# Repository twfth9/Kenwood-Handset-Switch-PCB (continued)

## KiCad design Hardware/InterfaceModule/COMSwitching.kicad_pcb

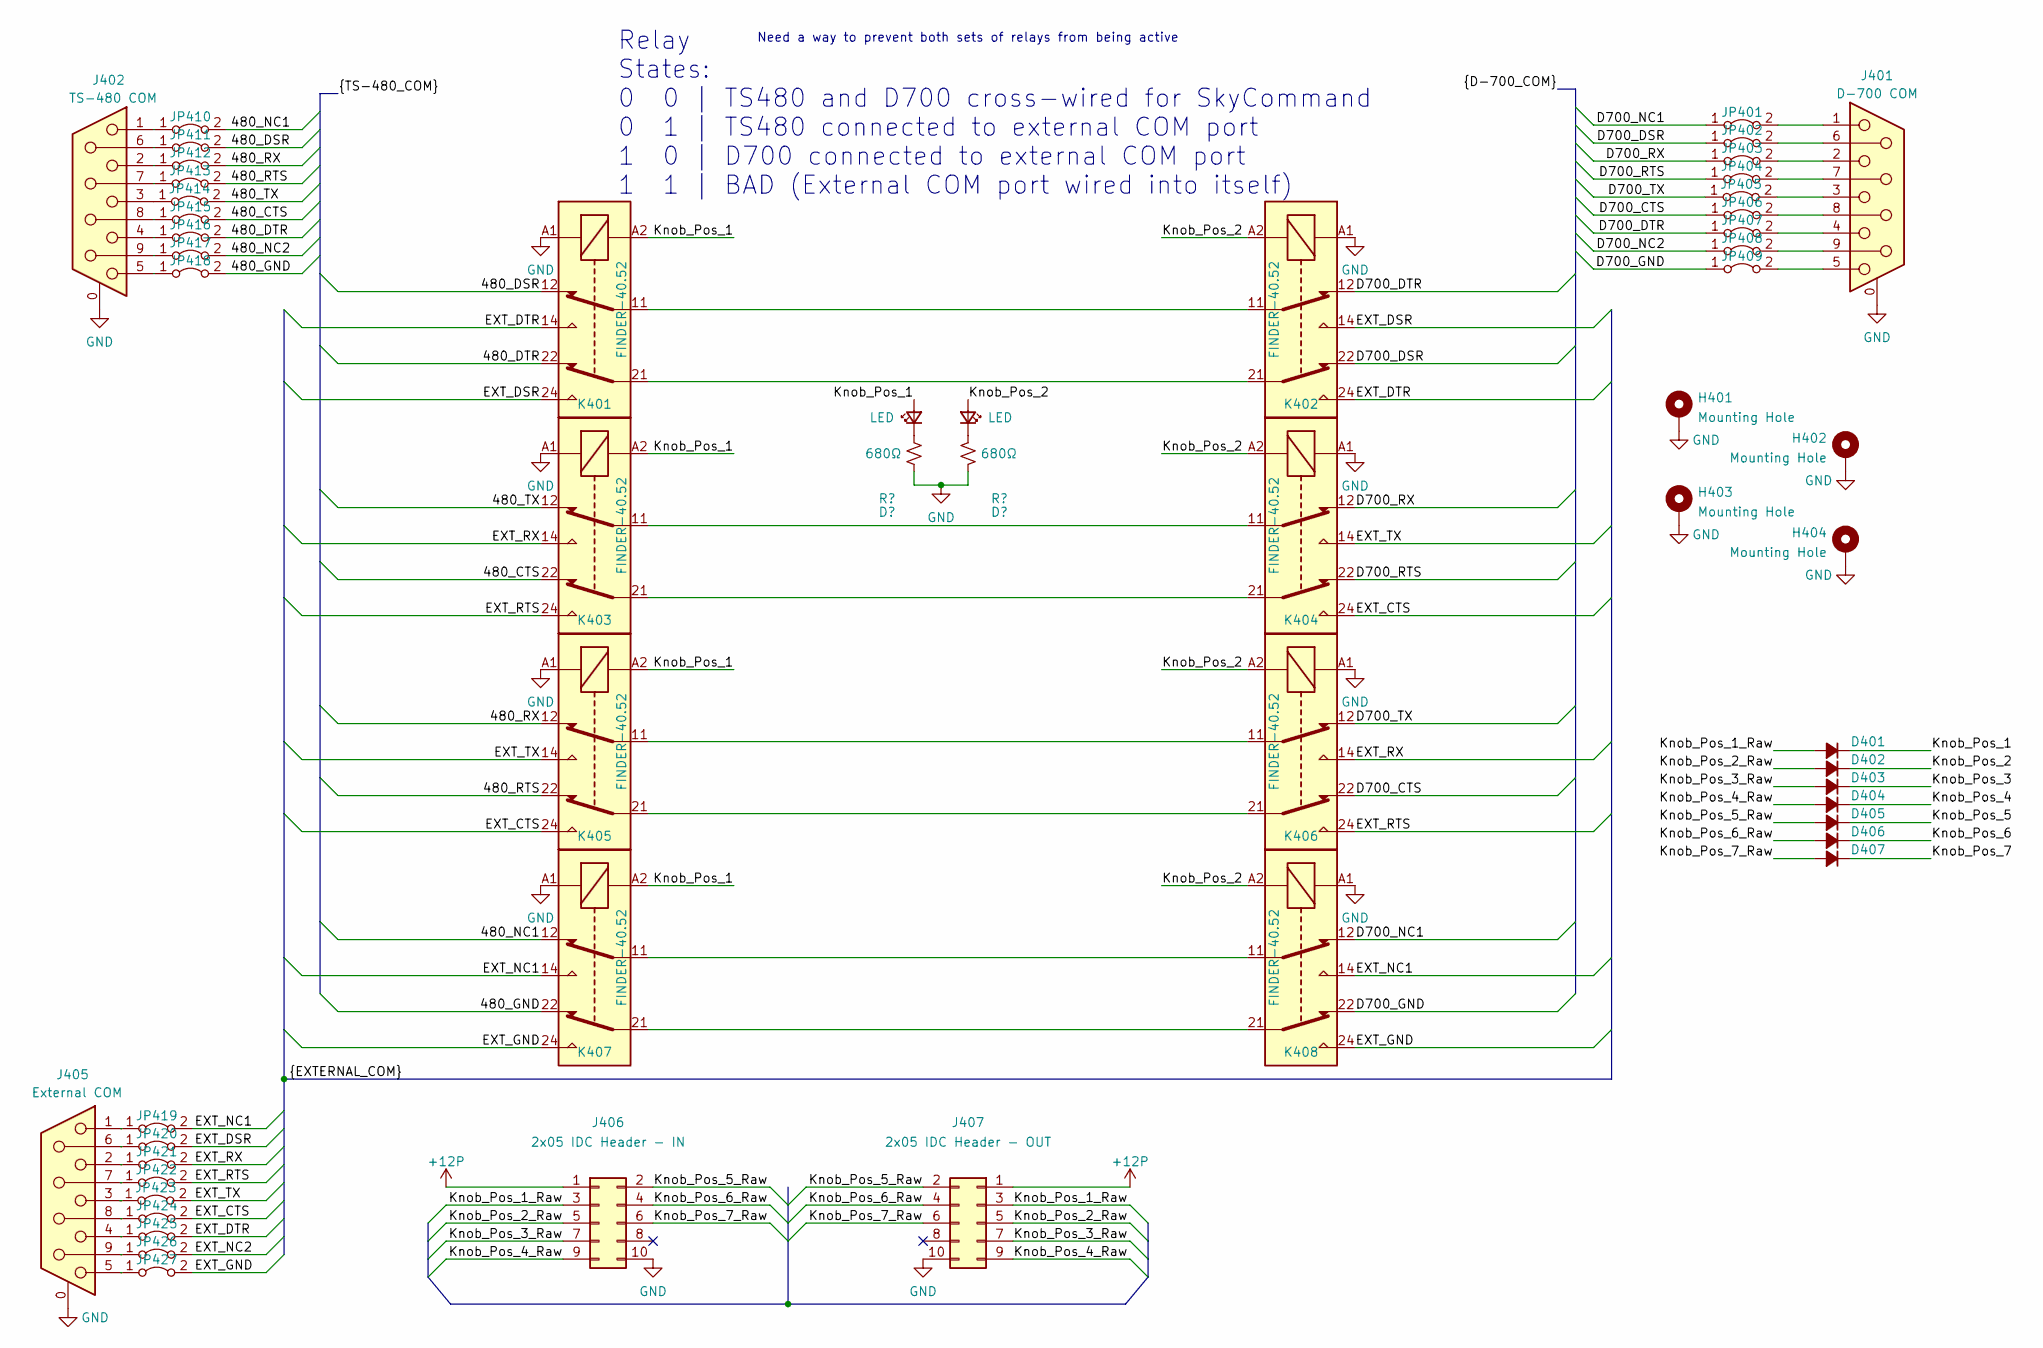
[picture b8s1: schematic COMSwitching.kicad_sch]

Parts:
D401, D402, D403, D404, D405, D406, D407: D_Small_Filled; D_A-405_P2.54mm_Vertical_AnodeUp
H401, H402, H403, H404: Mounting Hole; M3_Mounting
J401: D-700 COM; DSUB-9_Male_Horizontal_P2.77x2.84mm_EdgePinOffset7.70mm_Hou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
J402: TS-480 COM; DSUB-9_Male_Horizontal_P2.77x2.84mm_EdgePinOffset7.70mm_Hou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
J405: External COM; DSUB-9_Male_Horizontal_P2.77x2.84mm_EdgePinOffset7.70mm_Hou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
J406: 2x05 IDC Header - IN; IDC-Header_2x05_P2.54mm_Vertical
J407: 2x05 IDC Header - OUT; IDC-Header_2x05_P2.54mm_Vertical
JP401, JP402, JP403, JP404, JP405, JP406, JP407, JP408, JP409, JP410, JP411, JP412, JP413, JP414, JP415, JP416, JP417, JP418, JP419, JP420, JP421, JP422, JP423, JP424, JP425, JP426, JP427: Jumper_2_Bridged; 1.0mm_Bridge
K401, K402, K403, K404, K405, K406, K407, K408: FINDER-40.52; Relay_DPDT_Finder_30.22

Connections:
+12P: J406.1, J407.1
/COM Port Switching/480_CTS: JP415.2 (B), K403.22
/COM Port Switching/480_DSR: JP411.2 (B), K401.12
/COM Port Switching/480_DTR: JP416.2 (B), K401.22
/COM Port Switching/480_GND: JP418.2 (B), K407.22
/COM Port Switching/480_NC1: JP410.2 (B), K407.12
/COM Port Switching/480_NC2: JP417.2 (B)
/COM Port Switching/480_RTS: JP413.2 (B), K405.22
/COM Port Switching/480_RX: JP412.2 (B), K405.12
/COM Port Switching/480_TX: JP414.2 (B), K403.12
/COM Port Switching/D700_CTS: JP406.1 (A), K406.22
/COM Port Switching/D700_DSR: JP402.1 (A), K402.22
/COM Port Switching/D700_DTR: JP407.1 (A), K402.12
/COM Port Switching/D700_GND: JP409.1 (A), K408.22
/COM Port Switching/D700_NC1: JP401.1 (A), K408.12
/COM Port Switching/D700_NC2: JP408.1 (A)
/COM Port Switching/D700_RTS: JP404.1 (A), K404.22
/COM Port Switching/D700_RX: JP403.1 (A), K404.12
/COM Port Switching/D700_TX: JP405.1 (A), K406.12
/COM Port Switching/EXT_CTS: JP424.2 (B), K404.24, K405.24
/COM Port Switching/EXT_DSR: JP420.2 (B), K401.24, K402.14
/COM Port Switching/EXT_DTR: JP425.2 (B), K401.14, K402.24
/COM Port Switching/EXT_GND: JP427.2 (B), K407.24, K408.24
/COM Port Switching/EXT_NC1: JP419.2 (B), K407.14, K408.14
/COM Port Switching/EXT_NC2: JP426.2 (B)
/COM Port Switching/EXT_RTS: JP422.2 (B), K403.24, K406.24
/COM Port Switching/EXT_RX: JP421.2 (B), K403.14, K406.14
/COM Port Switching/EXT_TX: JP423.2 (B), K404.14, K405.14
/COM Port Switching/Knob_Pos_1: D401.1 (K), K401.A2, K403.A2, K405.A2, K407.A2; also elsewhere on the board
/COM Port Switching/Knob_Pos_1_Raw: D401.2 (A), J406.3, J407.3
/COM Port Switching/Knob_Pos_2: D402.1 (K), K402.A2, K404.A2, K406.A2, K408.A2; also elsewhere on the board
/COM Port Switching/Knob_Pos_2_Raw: D402.2 (A), J406.5, J407.5
/COM Port Switching/Knob_Pos_3: D403.1 (K)
/COM Port Switching/Knob_Pos_3_Raw: D403.2 (A), J406.7, J407.7
/COM Port Switching/Knob_Pos_4: D404.1 (K)
/COM Port Switching/Knob_Pos_4_Raw: D404.2 (A), J406.9, J407.9
/COM Port Switching/Knob_Pos_5: D405.1 (K)
/COM Port Switching/Knob_Pos_5_Raw: D405.2 (A), J406.2, J407.2
/COM Port Switching/Knob_Pos_6: D406.1 (K)
/COM Port Switching/Knob_Pos_6_Raw: D406.2 (A), J406.4, J407.4
/COM Port Switching/Knob_Pos_7: D407.1 (K)
/COM Port Switching/Knob_Pos_7_Raw: D407.2 (A), J406.6, J407.6
GND: H401.1, H402.1, H403.1, H404.1, J401.0 (PAD), J402.0 (PAD), J405.0 (PAD), J406.10, J407.10, K401.A1, K402.A1, K403.A1, K404.A1, K405.A1, K406.A1, K407.A1, K408.A1; also elsewhere on the board
unnamed: J401.1, JP401.2 (B)
unnamed: J401.2, JP403.2 (B)
unnamed: J401.3, JP405.2 (B)
unnamed: J401.4, JP407.2 (B)
unnamed: J401.5, JP409.2 (B)
unnamed: J401.6, JP402.2 (B)
unnamed: J401.7, JP404.2 (B)
unnamed: J401.8, JP406.2 (B)
unnamed: J401.9, JP408.2 (B)
unnamed: J402.1, JP410.1 (A)
unnamed: J402.2, JP412.1 (A)
unnamed: J402.3, JP414.1 (A)
unnamed: J402.4, JP416.1 (A)
unnamed: J402.5, JP418.1 (A)
unnamed: J402.6, JP411.1 (A)
unnamed: J402.7, JP413.1 (A)
unnamed: J402.8, JP415.1 (A)
unnamed: J402.9, JP417.1 (A)
unnamed: J405.1, JP419.1 (A)
unnamed: J405.2, JP421.1 (A)
unnamed: J405.3, JP423.1 (A)
unnamed: J405.4, JP425.1 (A)
unnamed: J405.5, JP427.1 (A)
unnamed: J405.6, JP420.1 (A)
unnamed: J405.7, JP422.1 (A)
unnamed: J405.8, JP424.1 (A)
unnamed: J405.9, JP426.1 (A)
unnamed: K401.11, K402.11
unnamed: K401.21, K402.21
unnamed: K403.11, K404.11
unnamed: K403.21, K404.21
unnamed: K405.11, K406.11
unnamed: K405.21, K406.21
unnamed: K407.11, K408.11
unnamed: K407.21, K408.21

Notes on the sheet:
Need a way to prevent both sets of relays from being active
Relay States: 0 0 | TS480 and D700 cross-wired for SkyCommand 0 1 | TS480 connected to external COM port 1 0 | D700 connected to external COM port 1 1 | BAD (External COM port wired into itself)

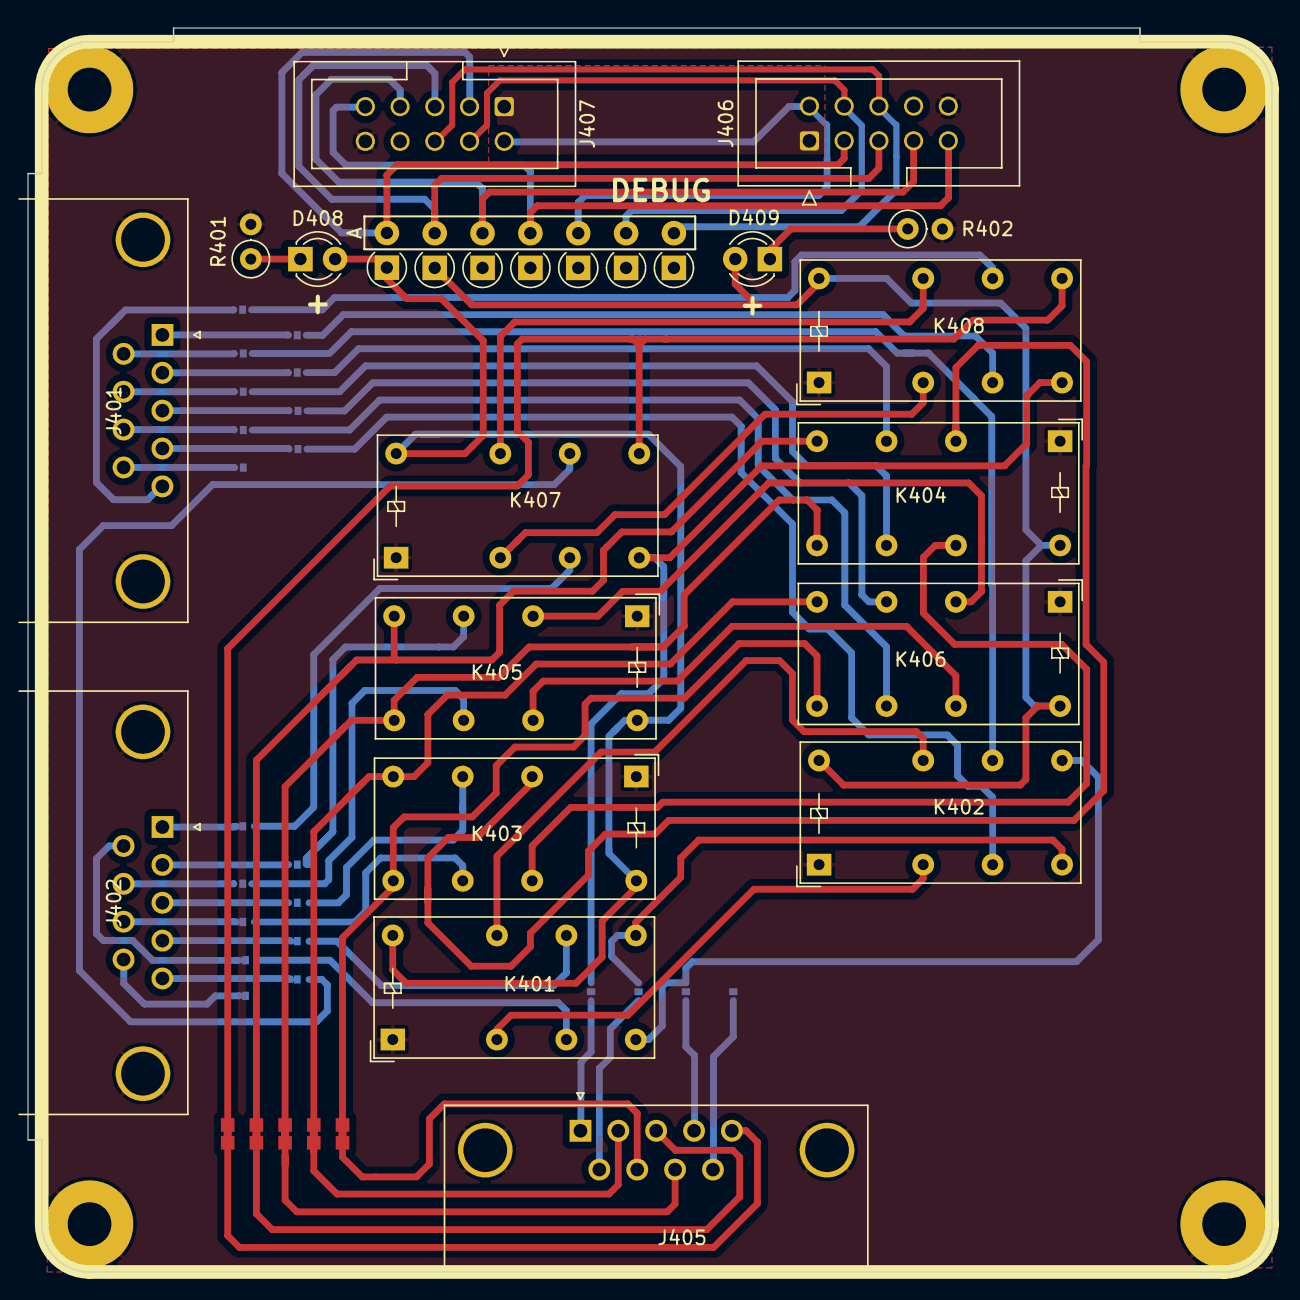
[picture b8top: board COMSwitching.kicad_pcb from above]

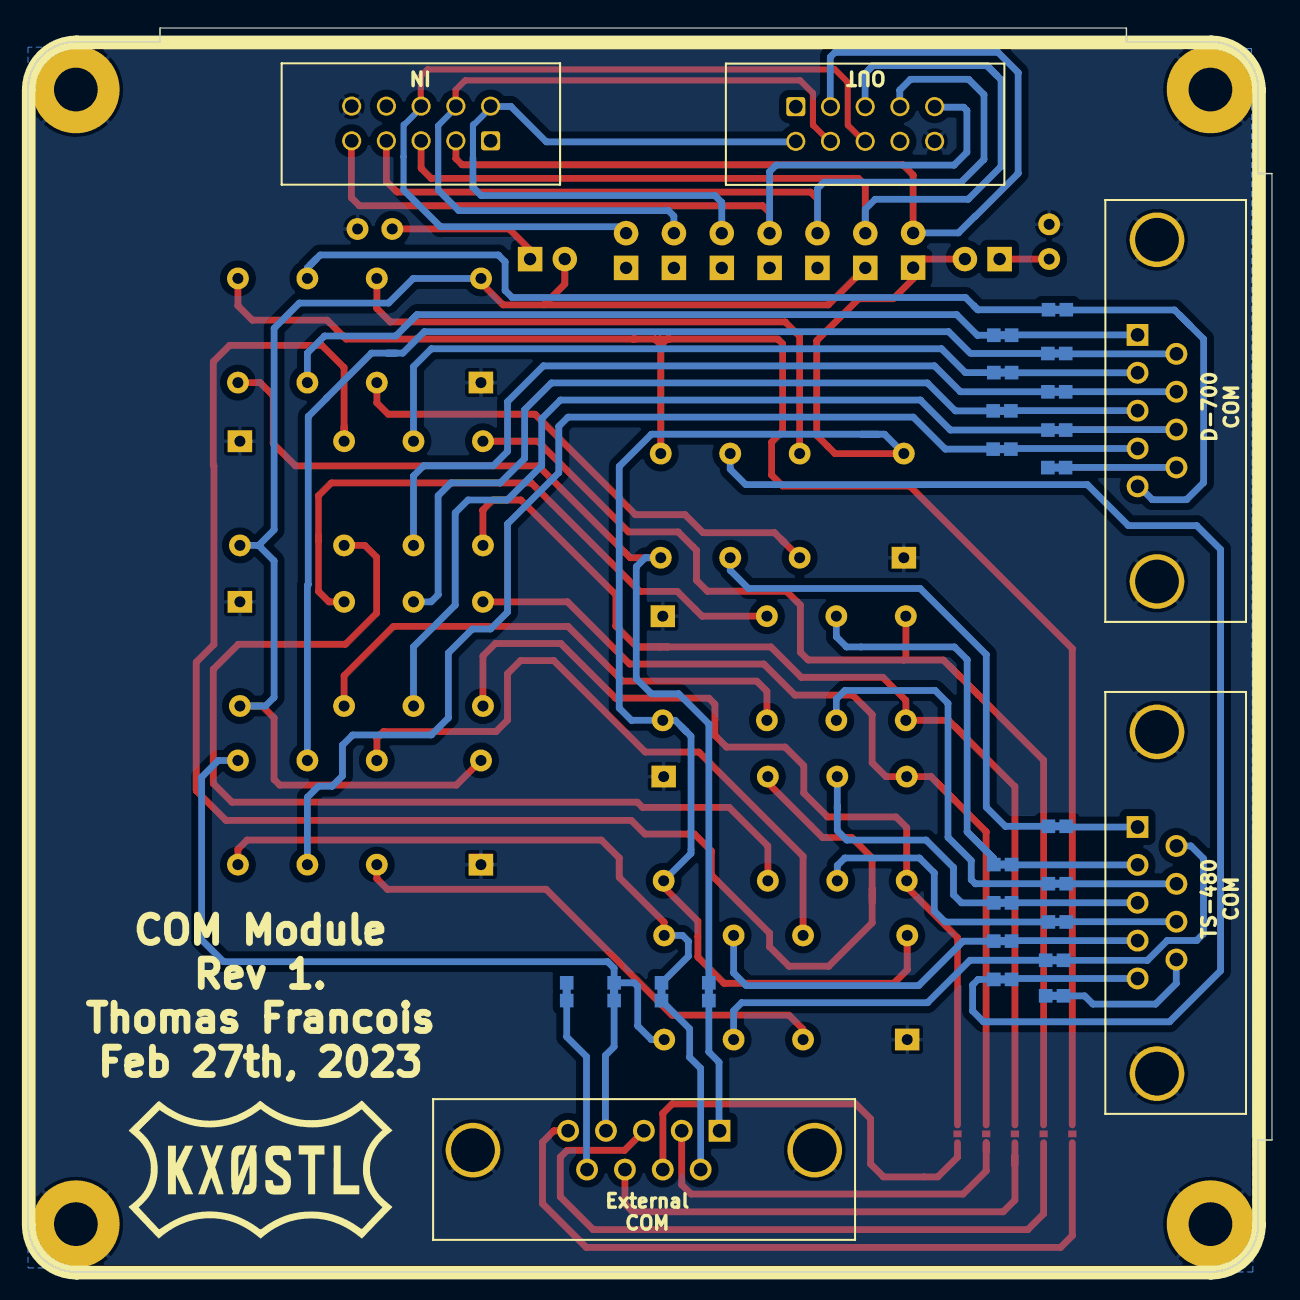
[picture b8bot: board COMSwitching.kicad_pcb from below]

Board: 2 copper layers, 91.0 x 91.0 mm, 55 parts (22 on the bottom side), 72 nets.

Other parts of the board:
D408, D409: LED; LED_D3.0mm
R401, R402: 680Ω; R_Axial_DIN0207_L6.3mm_D2.5mm_P2.54mm_Vertical

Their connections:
/COM Port Switching/Knob_Pos_1: D408.2 (A); also elsewhere on the board
/COM Port Switching/Knob_Pos_2: D409.2 (A); also elsewhere on the board
GND: R401.2, R402.2; also elsewhere on the board
unnamed: D408.1 (K), R401.1
unnamed: D409.1 (K), R402.1

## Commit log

2023-01-16 Created rough PCB
    GND on one relay needs to be fixed
2023-01-16 Updated layout, fixed ground islands
2023-01-29 Adjusted trace spacings
2023-01-30 Created PCB for KrakenSDR disconnect relay board, rearranged file structure
2023-01-30 New design as passthrough Kraken hat
2023-01-30 Created slim THRU and daughterboard cover
2023-01-30 Created ThinThru version of the board
2023-01-31 Created master switching pcb, com and mic relay circuits
2023-02-01 Connections for data ports, gps, improved mic connections
2023-02-01 Picked some footprints for most connectors
2023-02-02 Redesigned layout and labels
2023-02-02 More cleaning
2023-02-04 Fixed labels
    I don't know how to do busses properly, oh well
2023-02-04 Added selector input
2023-02-04 Replaced all relays with DPDT
2023-02-12 Broke out switching to individual boards
2023-02-20 Added backplane between boards, redesigned selector
2023-02-20 Initial routings of data and main boards
2023-02-20 Routed mic board
2023-02-21 Rerouted main and mic boards
    Might redo main board, it works but looks gross
2023-02-22 Routed data board
2023-02-26 Finished routing all 4 boards
2023-02-26 Complete routing, added debug pads/bridges
2023-02-26 Panelized boards
2023-02-26 Tweaked some things
2023-02-26 Tweaked more things
2023-02-26 Tweaks
2023-02-26 Even more tweaks
2023-02-26 cleaned some traces, changed tolerances, and copper pours
2023-02-27 Added LEDs
2023-03-04 Added silkscreen logos
2023-03-04 Generated gerber files
2023-03-05 Updated silkscreen dates, corrected gerber files
2023-12-29 Panel Dimensions to PCB
2023-12-29 Initial Schematic Work
2023-12-29 Schematic progress
2024-01-01 Added Instrumentation Amplifier To Schematic
2024-01-01 Assigned footprints, expanded schematic
2024-01-02 Changed to 14-segement Characters
2024-01-03 Added to schematic
2024-01-03 Added footprints and sectioned the schematic
    Still need to make sub pages and make a footprint for the MAX chips
2024-01-03 Scooted some stuffs
2024-01-03 Adjusted mode LEDs
2024-01-03 Added footprints to pcb file
    Need a proper footprint for the 14-seg LEDs, MAX driver chips...and something else that I can't remember right now
2024-01-08 Organized schematic into two pages, begun PCB routing
2024-01-08 Finished routing of rear board
2024-01-09 Routed most of the front panel
2024-01-10 Most of top board is routed
2024-01-10 beep
2024-01-14 Finished routing front panel
    Realized that I don't know how optocouplers work, so I need to replace them with transistors or something now
2024-01-14 Beginning to transition to BJTs
2024-01-15 Fixed BJT math
2024-01-15 Almost done with routing
2024-01-15 Finished routing
    Now just need to combine the boards with mousebites
2024-01-15 Modified front board to include cutout for rotate pot
2024-01-18 Rearranged pcb into production form, moved connector on top board
2024-04-05 Small tweaks to PCB
2024-04-07 More tweaks and silkscreen labels
2025-06-02 Audio Panel Progress
2025-06-03 Fixed undefined LED_IN net
2025-06-04 Added subsheets for audio panel
2025-06-04 Added symbols for crosspoint switches
2025-06-05 Added MT8816 crosspoint switch subsheet
2025-06-07 Added headphone and speaker jack interfaces
2025-06-09 Added crosspoints for each connector
2025-06-11 Added stupid Up,Down,PTT switching circuits
    I realize now this is very stupid, and I should just do this with a single GPIO expander IC
2025-06-11 Added MIC port protection
2025-06-12 Added MIC port protections
2025-06-12 Added 232 protections
2025-06-13 Early attempt at COM switching ideas
2025-06-13 Created COM switching using bilateral switches
    This feels stupid...but these chips are really cheap and actually pretty small. I know I say it now, but I'll pay for it when it comes time to do the routing :P
2025-06-13 Revisiting the audio input buffer circuit
2025-06-15 Added DSP chips, practicing with bus lines
2025-06-16 Added group labels
2025-06-16 Added MIC PTT UP DOWN sensing and buffering
2025-06-16 Replaced microphone page bs with an ADC and DAC
2025-06-17 Simplified COM switching, added USB-232
2025-06-17 small stuff
2025-06-17 Added main +5V supply with current sensing
2025-06-17 Added ideal diode controller to main power input
2025-06-18 Adding ADAV400 sheet
2025-06-18 Added USB hub, completed ADAV400 sheet, working on USBi programmer connections
2025-06-18 Added initial DB audio out connector
    Need to pick the best way to convert single-ended audio to differential
2025-06-18 Realized that I need to rethink how I'm going to mix the radio audio with the stereo audio
2025-06-19 Added MT8816 for audio switching
2025-06-19 Adjusted MIC input to crosspoint switch
2025-06-20 Added DATA switching to COM switching page
2025-06-20 Cleaned up stuff, defined more busses
2025-06-20 Removed extraneous pages
2025-06-20 Laid groundwork for stereo DSP routing
    I figured it out. I need to combine the left audio channels, combine the right audio channels, pass both to the DSP chips. Each audio zone will eventually have its own DSP to handle crossovers and ti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
    Use the Pioneer Network Mode for easier frequency separation.
    To do: add active summing amplifers to combine left and right sub-channels
2025-06-20 Added audio sum amplifiers
2025-06-21 Added speaker and headphone audio switching
2025-06-22 I forgot what I changed today, but it was some stuff
2025-06-23 Cleaned up sheet voltage inputs
2025-06-23 Considering replacing some of the MCP23017s with 74HC594 shift register
    Ken KC9UMR gave me this idea, would be cheaper option
2025-06-25 Added PCM2904 audio codec
2025-06-30 Moved files around, getting ready to design development modules
2025-06-30 Added microphone switcher initial schematic
2025-07-06 Finished most if not all of the microphone dev board
2025-07-07 Removed DAC and buffers for PTT, added PTT LEDs and inverters
2025-07-08 Assigned (most) footprints
2025-07-08 Changed LEDs to 0603 SMDs
2025-07-08 Rearranged LEDs, placed components onto PCB file
2025-07-08 Missed some LEDs, now SMD
2025-07-08 Changed WS2813Bs to WS2812B-2020s
    To reduce footprint size
2025-07-08 Changed resistor arrays to SMD
2025-07-09 Added stuff and things
2025-07-09 Finished assigning footprints
    No errors in PCB import, woo!
2025-07-09 Fixed 3bridge footprint
    Removed solder mask between pads
2025-07-09 Removed silkscreen component identifiers
2025-07-11 Started work on COM switching dev board
2025-07-11 Added power and USB serial
2025-07-12 Replaced MCPs with SAMD21G15
    The I2C bus was going to be too slow to handle the 232 timing required. I couldn't think of a cheaper way of doing it than just throwing a SAMD on there and calling it a day
2025-07-13 Added USB hub, new inverting LED indicator
2025-07-13 Added some stuff, don't remember what
2025-07-13 Fixed some more stuff
2025-07-13 Defined footprints for every component
2025-07-13 More things
2025-07-14 Assigned footprints
2025-07-14 Added test points for data ports, for real this time
2025-07-15 Adding shift registers to COM swicher
2025-07-16 Added shift registers to SPI
2025-07-16 Started replacing MCP23017 with shift registers
2025-07-16 Added stuff
    I just realized that the UP, DWN, PTT buttons should be powered by the radios.
    This means that I can get rid of the DAC, and just output to a voltage divider to generate the voltages.
    The radios have tons of 47k resistors on these lines so driving a lot of current isn't a requirement
2025-07-17 added stuff
2025-07-19 Changing mic switcher to use shift registers
2025-07-20 Finished most of microphone switcher circuit
    I'm very happy with where this is right now, I don't see anything immediately out of place and the schematic is now pretty well organized
2025-07-21 Isolated mic outputs to their respective radios
    Button presses are easy to isolate with optocouplers, I'm coupling in the mic signals using dc blocking capacitors and generating the bias voltages from the respective radios
2025-07-21 Added esd diodes to mic lines
    This shouldn't effect the audio signal because the voltage is +-5mV at this point, and the diode standoff voltages are at 5V
2025-07-22 Added labeling and organized pages
2025-07-22 COM Swicher changes and MIC Switcher changes
    COM: Added labels to schematic sections, changed footprint of level shifters
    MIC: Added test points to MIC audio path
2025-07-22 Added some more test points to MIC path
2025-07-23 Added protection to DATA switcher, changed filter cutoffs
2025-07-23 Added some data switching stuff
2025-07-24 Beginning adding 8x8 matrix switch design for data switcher
2025-07-25 Improved switching logic
2025-07-25 Improved DC bias circuit
2025-07-25 Simplified data port stuff
    I was trying to amplify and attenuate the input signal, but I need to remember that this board is just for switching. OpAmps are included for buffering through crosspoint, but that's it
2025-07-25 Added data lowpass filter stuffs
2025-07-26 Adjusted I2C addresses and component identifiers
2025-07-26 Several small changes
    I realize now that having the switched 9600 and 1200 audio lines is stupid. I'm going to remove this in future revisions and will replace it with USB audio chips...maybe...
2025-07-27 Small tweaks
2025-07-27 Fixed pullup/dwn resistors, rotated optoisolator on MIC PTT outs
2025-07-28 DATA switcher put together
2025-07-28 Beginnings of front IO panel dev module
2025-07-29 Adding LEDs
2025-07-29 Moved LEDs to pushbutton page
2025-07-31 Added level shifters for all SAMD21s
2025-07-31 Started downsizing from 8x8 to 4x4 crosspoint
2025-08-04 Many tweaks
2025-08-04 Added footprints for the missing
2025-08-13 IO Panel Progress
2025-08-15 Work on front control panel
2025-08-19 Fixed ESD chip on microcontroller I2C
2025-08-20 Fixed some footprints
2025-08-20 Changed DB9 connectors to stacked
2025-08-21 Fixed value of RADIO SQUELCH low-pass filter cap
2025-08-21 Fixed I2C pullups to 3V3
2025-08-22 Re-organized pull up/dwn resistors in schematic
2025-08-22 Changed encoder, added footprints for buttons
2025-08-22 Reorganized PISO bits
2025-08-22 Changed passives to Worthington footprints
2025-08-22 Added more LEDs
2025-08-22 Changed passives to Worthingtons
2025-08-22 Resized some resistors
2025-08-23 Fixed footprint errors, placed onto PCBs
2025-08-23 Added some 3D models
    Need to decide if I want to make every LED be SMD or keep just the power rails as through hole...
    I also need to go about seeing if I can find some resistor arrays in 0805 size because 1206 is huuuge
2025-08-23 Changed LED and Resistor Array packages
2025-08-23 Fixed crystal footprints
2025-08-23 Added edge cut board dimensions
    I've added a rectangle to the user comments layer which denotes the dimensions for a 1-DIN stereo PCB.
    I would like to fit the components onto a 100x100 mm board so my order can be cheap from JLCPCB, but it's going to be tricky so we'll see
2025-08-23 Tweaked SAMD21 footprint, added THT version
2025-08-23 Changed SAMD21 to through-hole footprint
2025-08-23 Initial PCB layouts
    Oh god...this is going to take a while...
    I'd like to try to get these to fit inside 100x100 mm, and they very well might be able to. I need to learn a good technique for soldering onto both sides of the board, likely using a reflow oven but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
2025-08-27 Routing progress
